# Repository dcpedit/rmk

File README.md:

# r/mk keyboard

The r/mk is a "keyboard" that mimics the style of the r/mk stickers that are floating around out there.

I got the idea of using plate mount MX stabalizers to go with the Choc v2 switch from Gimbal in this post:
https://www.keebtalk.com/t/new-kailh-choc-v2-switches/8349/22

If you use MX switches, you will need to use a plate with plate mount stabs, or skip the stabs altogether.

The switch footprints are from this project: https://github.com/luke-schutt/Pi5Keyboard. They support Kailh Choc V1, V2, Gateron low profile, and MX switches

And finally, the schematic and wiring for the rp2040 was taken from this project: https://github.com/Sleepdealr/RP2040-designguide

## Layout and pics

[Keyboard Layout Editor (KLE) link](http://www.keyboard-layout-editor.com/#/gists/66ec27985efc342d9c4acf2d43243eb4)

[Image gallery](https://imgur.com/a/in2jYlU)
## Stabalizer installation for Choc v2 switches

The installation of the stab wire is a bit tricky since it needs to go under the PCB.  This is the procedure I followed.

First, snap the stabalizer housing into the PCB without the stem or wire assembled.

Next, insert the stems into the housing.

Finally, you'll need to squeeze the wire in between the PCB and plastic "clip" so that it can be pushed into place.  You may need to lift the clip with a flat tool to create a gap, and apply a bit of force to get the wire in place.

## Case assembly

| Part                        | Count | Notes |
|-----------------------------|-------|-------|
| 3mm acrylic                 | 6     |
| Acrylic cement              | 1     | [Link](https://a.co/d/a8NEyjm)
| 1.5mm double-sided foam tape| 1     |
| Thin double-sided tape      | 1     | [Link](https://a.co/d/aWlYKNr)
| Adhesive rubber feet        | 4     | [Link](https://www.etsy.com/listing/1327182543/vath-self-adhesive-silicone-rubber-feet)

The case featured in the photo is made of 6 layers of 3mm acrylic glued together.  You'll need to cut all 6 layers numbered #1 through #6 in the `case.ai` Illustrator file in the `assets` folder.  I used Choc v2 low profile switches for this build, but if you use taller switches (ex Cherry MX), you may want to add an extra `#2 Top spacer` layer to hide the gap.

1) Glue layers #1 through #5 together with acrylic glue of your choice (I use Weld-On).  
2) Cut 2 squares of foam tape and place them on the PCB where the corner blockers are.  Make sure the tape is completely hidden by the blockers.
3) Stick the PCB to the top of the case, pushing down on the area where the foam tape is.
4) Cut strips of the thin double sided tape and place them around the bottom edge of the case.
5) Line up the bottom layer (#6) and press it into place.
6) Place the rubber feet in each corner of the bottom of the case.

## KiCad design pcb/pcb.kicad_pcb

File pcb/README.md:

# rmk (r/mk) PCB

You can use the files in the `production` folder for JLCPCB

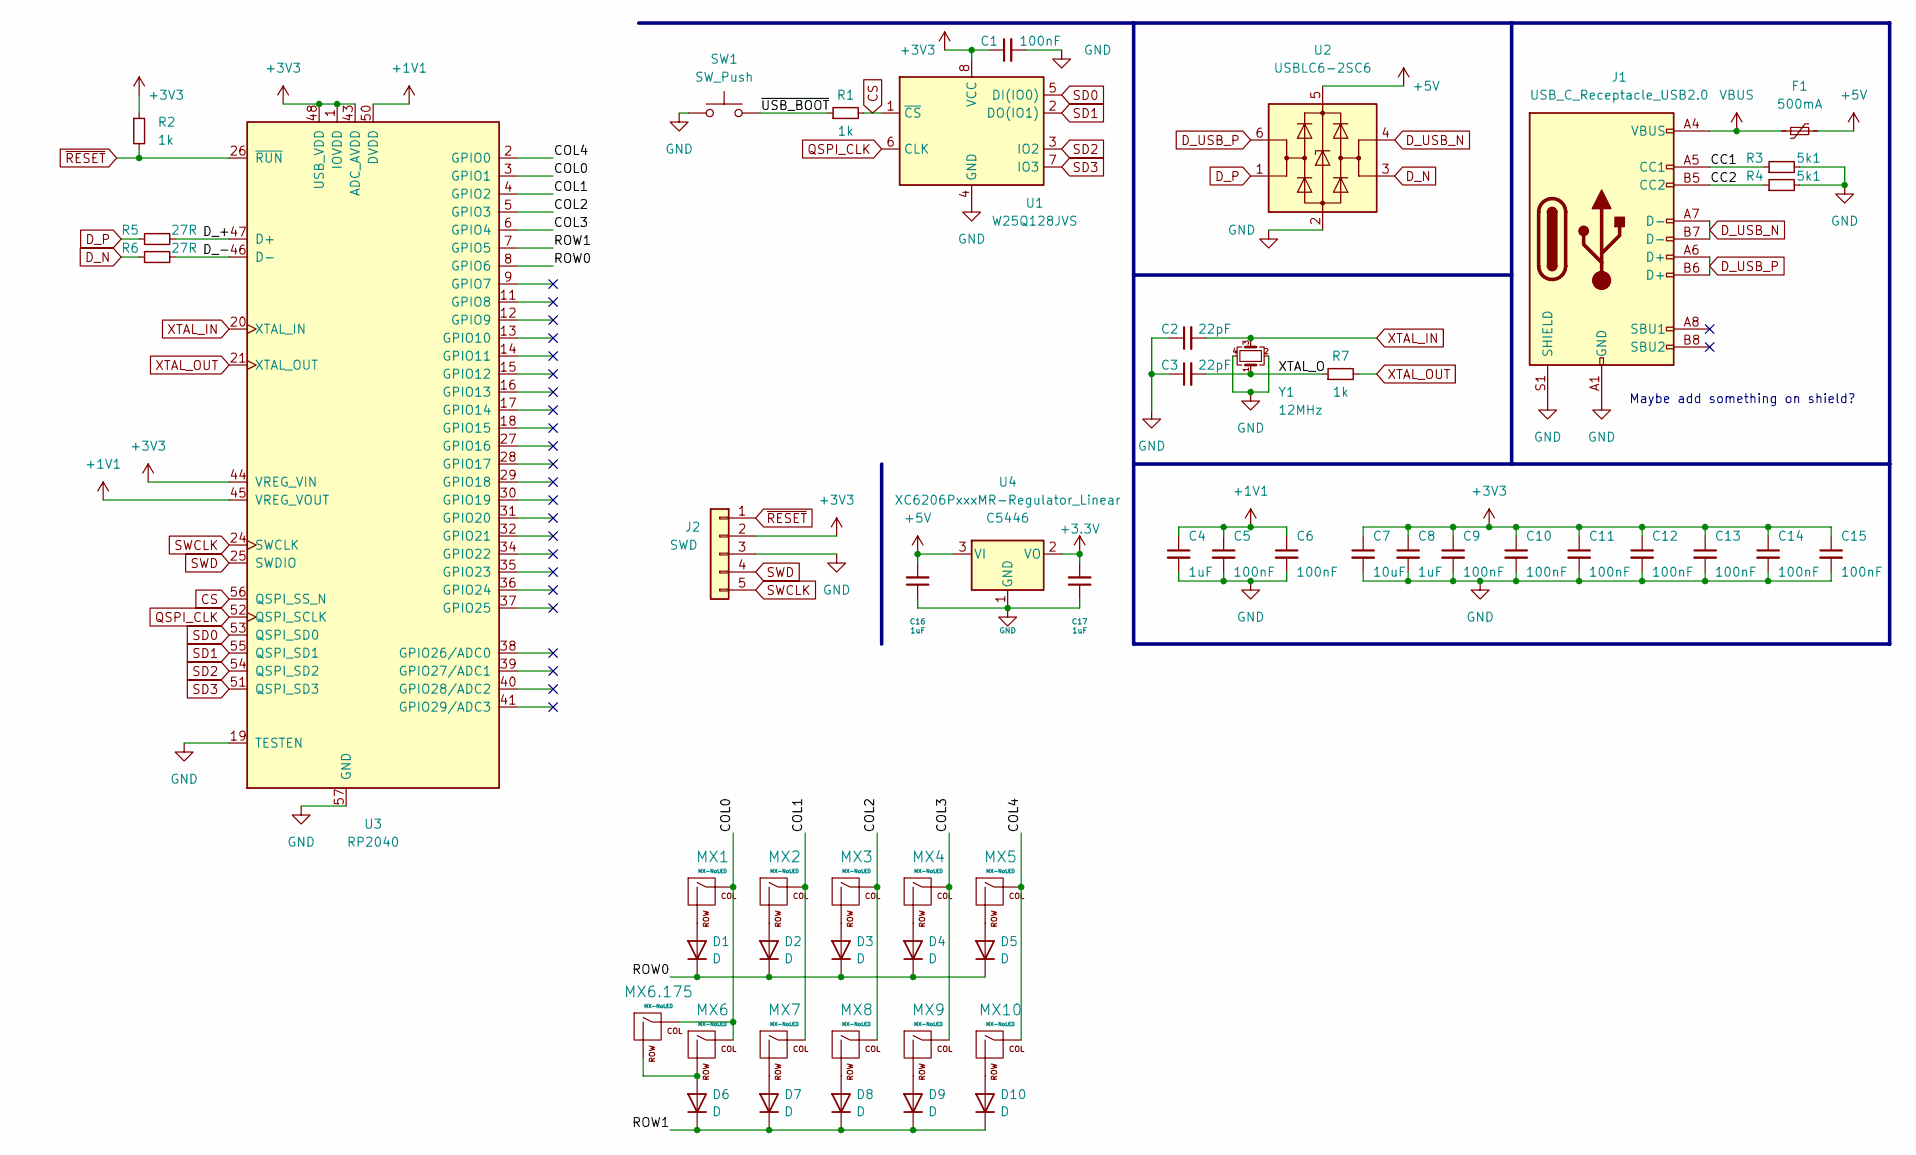
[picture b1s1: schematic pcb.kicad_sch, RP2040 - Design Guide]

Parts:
C1, C5, C6, C9, C10, C11, C12, C13, C14, C15: 100nF; C_0402_1005Metric; LCSC C1525
C2, C3: 22pF; C_0402_1005Metric; LCSC C1555
C4, C8, C16, C17: 1uF; C_0402_1005Metric; LCSC C52923
C7: 10uF; C_0402_1005Metric; LCSC C15525
D1, D2, D3, D4, D5, D6, D7, D8, D9, D10: D; LCSC C81598
F1: 500mA; Fuse_1206_3216Metric; LCSC C70076
J1: USB_C_Receptacle_USB2.0; USB_C_Receptacle_HRO_TYPE-C-31-M-12; LCSC C165948
J2: SWD; PinSocket_1x05_P2.54mm_Vertical
MX1, MX2, MX3, MX4, MX5, MX6, MX6.175, MX7, MX8, MX9, MX10: MX-NoLED
R1, R2, R7: 1k; R_0402_1005Metric; LCSC C11702
R3, R4: 5k1; R_0402_1005Metric; LCSC C25905
R5, R6: 27R; R_0603_1608Metric; LCSC C25190
SW1: SW_Push; PinSocket_1x02_P2.54mm_Vertical
U1: W25Q128JVS; SOIC-8_5.23x5.23mm_P1.27mm; LCSC C131025
U2: USBLC6-2SC6; SOT-23-6; LCSC C2827654
U3: RP2040; RP2040-QFN-56; LCSC C2040
U4: XC6206PxxxMR-Regulator_Linear; SOT-23; LCSC C5446
Y1: 12MHz; Crystal_SMD_3225-4Pin_3.2x2.5mm; LCSC C9002

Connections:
+1V1: C4.1, C5.1, C6.1, U3.23 (DVDD), U3.45 (VREG_VOUT), U3.50 (DVDD)
+5V: C16.2, F1.2, U2.5 (VBUS), U4.3 (VI)
/CC1: J1.A5 (CC1), R3.1
/CC2: J1.B5 (CC2), R4.1
/COL0: MX1.1 (COL), MX6.1 (COL), MX6.175.1 (COL), U3.3 (GPIO1)
/COL1: MX2.1 (COL), MX7.1 (COL), U3.4 (GPIO2)
/COL2: MX3.1 (COL), MX8.1 (COL), U3.5 (GPIO3)
/COL3: MX4.1 (COL), MX9.1 (COL), U3.6 (GPIO4)
/COL4: MX5.1 (COL), MX10.1 (COL), U3.2 (GPIO0)
/D_+: R5.2, U3.47 (D+)
/D_-: R6.2, U3.46 (D-)
/ROW0: D1.1 (K), D2.1 (K), D3.1 (K), D4.1 (K), D5.1 (K), U3.8 (GPIO6)
/ROW1: D6.1 (K), D7.1 (K), D8.1 (K), D9.1 (K), D10.1 (K), U3.7 (GPIO5)
/XTAL_O: C3.2, R7.1, Y1.1
/~USB_BOOT: R1.1, SW1.2
CS: R1.2, U1.1 (~CS), U3.56 (QSPI_SS_N)
D_N: R6.1, U2.3 (I/O2)
D_P: R5.1, U2.1 (I/O1)
D_USB_N: J1.A7 (D-), J1.B7 (D-), U2.4 (I/O2)
D_USB_P: J1.A6 (D+), J1.B6 (D+), U2.6 (I/O1)
GND: C1.2, C2.1, C3.1, C4.2, C5.2, C6.2, C7.2, C8.2, C9.2, C10.2, C11.2, C12.2, C13.2, C14.2, C15.2, C16.1, C17.1, J1.A1 (GND), J1.A12 (GND), J1.B1 (GND), J1.B12 (GND), J1.S1 (SHIELD), J2.3, R3.2, R4.2, SW1.1, U1.4 (GND), U2.2 (GND), U3.19 (TESTEN), U3.57 (GND), U4.1 (GND), Y1.2, Y1.4
unnamed: D1.2 (A), MX1.2 (ROW)
unnamed: D2.2 (A), MX2.2 (ROW)
unnamed: D3.2 (A), MX3.2 (ROW)
unnamed: D4.2 (A), MX4.2 (ROW)
unnamed: D5.2 (A), MX5.2 (ROW)
unnamed: D6.2 (A), MX6.2 (ROW), MX6.175.2 (ROW)
unnamed: D7.2 (A), MX7.2 (ROW)
unnamed: D8.2 (A), MX8.2 (ROW)
unnamed: D9.2 (A), MX9.2 (ROW)
unnamed: D10.2 (A), MX10.2 (ROW)
QSPI_CLK: U1.6 (CLK), U3.52 (QSPI_SCLK)
SD0: U1.5 (DI(IO0)), U3.53 (QSPI_SD0)
SD1: U1.2 (DO(IO1)), U3.55 (QSPI_SD1)
SD2: U1.3 (IO2), U3.54 (QSPI_SD2)
SD3: U1.7 (IO3), U3.51 (QSPI_SD3)
SWCLK: J2.5, U3.24 (SWCLK)
SWD: J2.4, U3.25 (SWDIO)
VBUS: F1.1, J1.A4 (VBUS), J1.A9 (VBUS), J1.B4 (VBUS), J1.B9 (VBUS)
XTAL_IN: C2.2, U3.20 (XTAL_IN), Y1.3
XTAL_OUT: R7.2, U3.21 (XTAL_OUT)
~RESET: J2.1, R2.2, U3.26 (~RUN)

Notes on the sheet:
Maybe add something on shield?

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
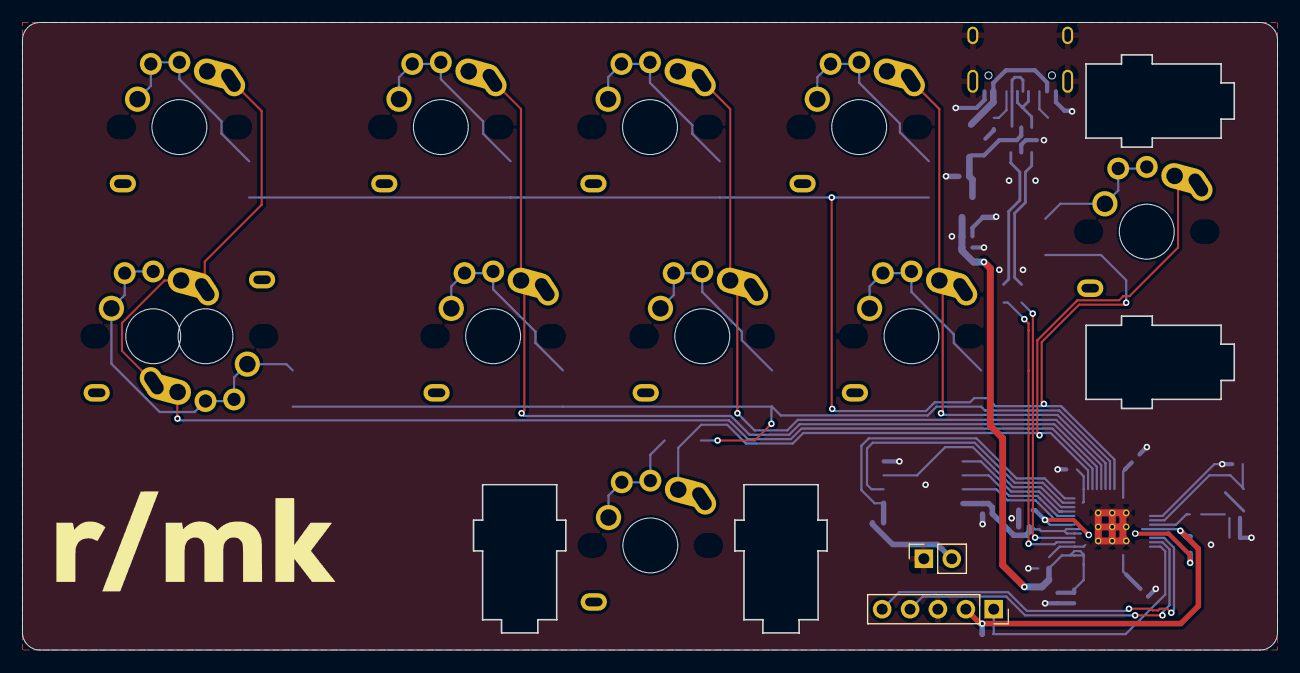
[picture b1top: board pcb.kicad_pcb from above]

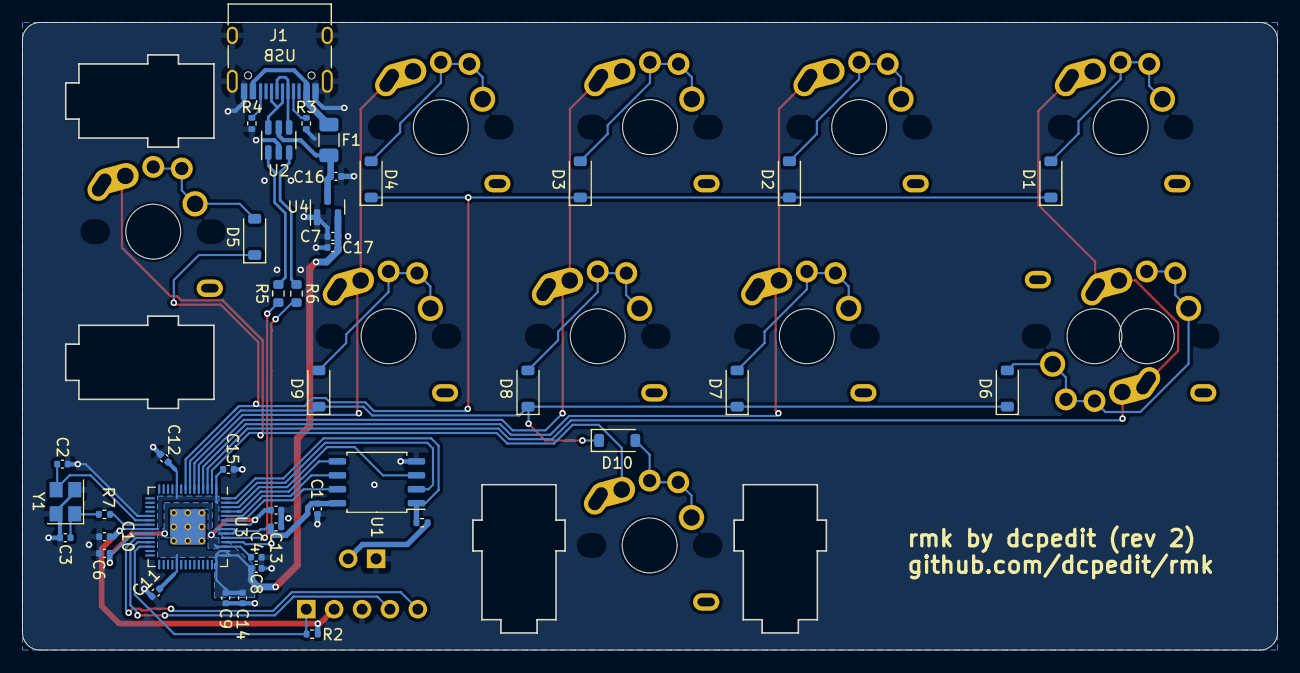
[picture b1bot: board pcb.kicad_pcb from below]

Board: 2 copper layers, 114.3 x 57.1 mm, 54 parts (41 on the bottom side), 43 nets.

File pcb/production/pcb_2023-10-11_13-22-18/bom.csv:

Designator,Footprint,Quantity,Value,LCSC Part #
"C1, C10, C11, C12, C13, C14, C15, C5, C6, C9",0402,10,100nF,C1525
"C16, C17, C4, C8",0402,4,1uF,C52923
"C2, C3",0402,2,22pF,C1555
C7,0402,1,10uF,C15525
"D1, D10, D2, D3, D4, D5, D6, D7, D8, D9",D_SOD-123,10,D,C81598
F1,1206,1,500mA,C70076
J1,USB_C_Receptacle_HRO_TYPE-C-31-M-12,1,USB_C_Receptacle_USB2.0,C165948
"MX1, MX10, MX2, MX3, MX4, MX5, MX6, MX6.175, MX7, MX8, MX9",Low Profile GC plus MX,11,MX-NoLED,
"R1, R2, R7",0402,3,1k,C11702
"R3, R4",0402,2,5k1,C25905
"R5, R6",0603,2,27R,C25190
U1,SOIC-8_5.23x5.23mm_P1.27mm,1,W25Q128JVS,C131025
U2,SOT-23-6,1,USBLC6-2SC6,C2827654
U3,RP2040-QFN-56,1,RP2040,C2040
U4,SOT-23,1,XC6206PxxxMR-Regulator_Linear,C5446
Y1,Crystal_SMD_3225-4Pin_3.2x2.5mm,1,12MHz,C9002

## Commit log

2023-10-11 Update README.md with images
2023-10-11 Add firmware and PCB readme
2023-10-11 Rearrange photos
2023-10-13 Add build steps
2023-10-13 Add image gallery
2023-10-13 Add link to firmware source
2023-10-13 Add pcb step file
